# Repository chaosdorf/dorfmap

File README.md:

# dorfmap-vue

## Project setup
```
yarn install
```

### Compiles and hot-reloads for development
```
yarn run serve
```

### Compiles and minifies for production
```
yarn run build
```

### Run your tests
```
yarn run test
```

### Lints and fixes files
```
yarn run lint
```

### Customize configuration
See [Configuration Reference](https://cli.vuejs.org/config/).

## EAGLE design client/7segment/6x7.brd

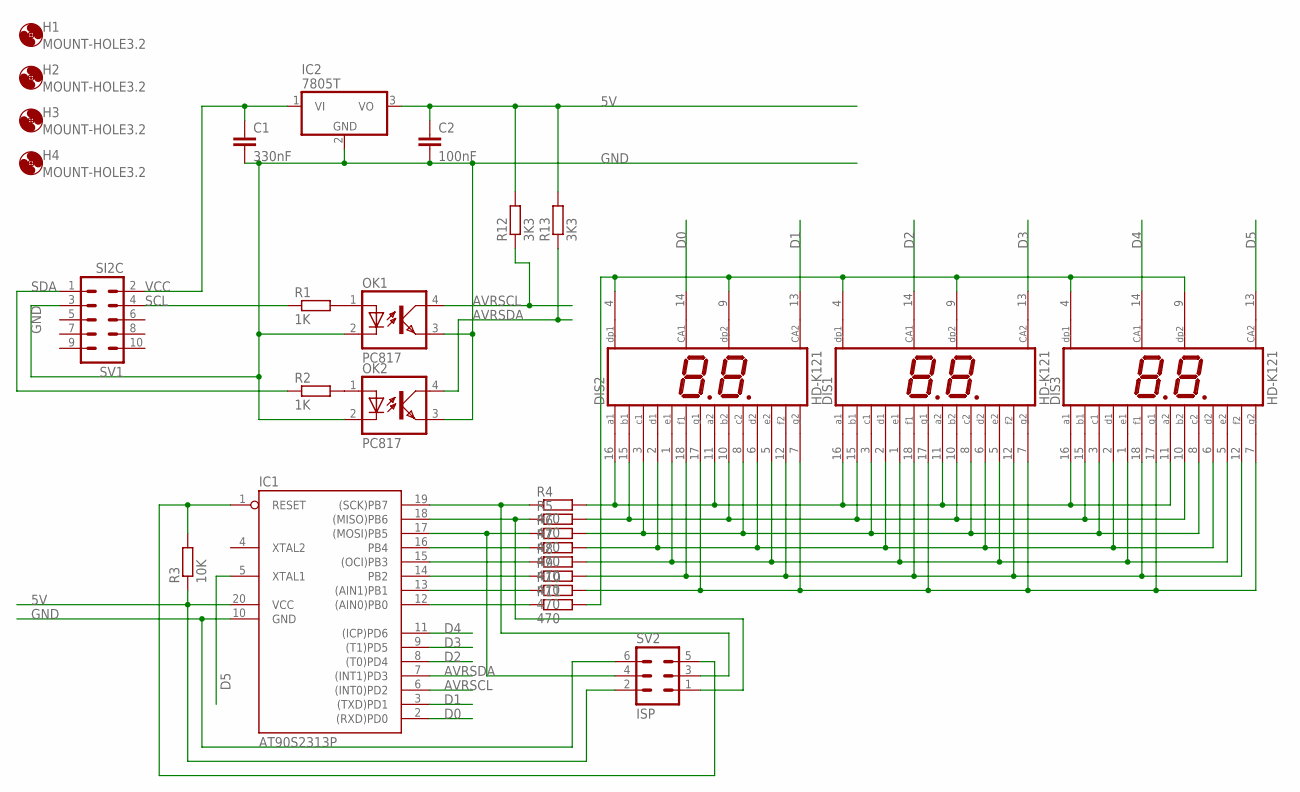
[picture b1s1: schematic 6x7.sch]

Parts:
C1: 330nF; C2.5-3
C2: 100nF; C050-024X044
DIS1, DIS2, DIS3: HD-K121; HDSP-R
H1, H2, H3, H4: MOUNT-HOLE3.2; 3,2
IC1: AT90S2313P; DIL20
IC2: 7805T; TO220H
OK1, OK2: PC817; DIL04
R1, R2: 1K; 0207/10
R3: 10K; 0207/10
R4, R5, R6, R7, R8, R9, R10, R11: 470; 0207/10
R12, R13: 3K3; 0207/10
SV1: SI2C; ML10
SV2: ISP; ML6

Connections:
5V: C2.1, IC1.20 (VCC), IC2.3 (VO), R3.1, R12.2, R13.2, SV2.2
AVRSCL: IC1.6 ((INT0)PD2), OK1.4 (COL), R12.1
AVRSDA: IC1.7 ((INT1)PD3), OK2.4 (COL), R13.1
D0: DIS2.14 (CA1), IC1.2 ((RXD)PD0)
D1: DIS2.13 (CA2), IC1.3 ((TXD)PD1)
D2: DIS1.14 (CA1), IC1.8 ((T0)PD4)
D3: DIS1.13 (CA2), IC1.9 ((T1)PD5)
D4: DIS3.14 (CA1), IC1.11 ((ICP)PD6)
D5: DIS3.13 (CA2), IC1.5 (XTAL1)
GND: C1.2, C2.2, IC1.10 (GND), IC2.2 (GND), OK1.2 (C), OK1.3 (EMIT), OK2.2 (C), OK2.3 (EMIT), SV1.3, SV2.6
unnamed: OK1.1 (A), R1.2
unnamed: IC1.19 ((SCK)PB7), R4.1, SV2.3
unnamed: IC1.1 (RESET), R3.2, SV2.5
unnamed: OK2.1 (A), R2.2
unnamed: IC1.18 ((MISO)PB6), R5.1, SV2.1
unnamed: DIS1.3 (C1), DIS1.8 (C2), DIS2.3 (C1), DIS2.8 (C2), DIS3.3 (C1), DIS3.8 (C2), R6.2
unnamed: IC1.17 ((MOSI)PB5), R6.1, SV2.4
unnamed: IC1.16 (PB4), R7.1
unnamed: IC1.15 ((OCI)PB3), R8.1
unnamed: DIS1.7 (G2), DIS1.17 (G1), DIS2.7 (G2), DIS2.17 (G1), DIS3.7 (G2), DIS3.17 (G1), R10.2
unnamed: DIS1.4 (DP1), DIS1.9 (DP2), DIS2.4 (DP1), DIS2.9 (DP2), DIS3.4 (DP1), DIS3.9 (DP2), R11.2
unnamed: IC1.14 (PB2), R9.1
unnamed: IC1.13 ((AIN1)PB1), R10.1
unnamed: IC1.12 ((AIN0)PB0), R11.1
unnamed: DIS1.11 (A2), DIS1.16 (A1), DIS2.11 (A2), DIS2.16 (A1), DIS3.11 (A2), DIS3.16 (A1), R4.2
unnamed: DIS1.10 (B2), DIS1.15 (B1), DIS2.10 (B2), DIS2.15 (B1), DIS3.10 (B2), DIS3.15 (B1), R5.2
unnamed: DIS1.2 (D1), DIS1.6 (D2), DIS2.2 (D1), DIS2.6 (D2), DIS3.2 (D1), DIS3.6 (D2), R7.2
unnamed: DIS1.1 (E1), DIS1.5 (E2), DIS2.1 (E1), DIS2.5 (E2), DIS3.1 (E1), DIS3.5 (E2), R8.2
unnamed: DIS1.12 (F2), DIS1.18 (F1), DIS2.12 (F2), DIS2.18 (F1), DIS3.12 (F2), DIS3.18 (F1), R9.2
SCL: R1.1, SV1.4
SDA: R2.1, SV1.1
VCC: C1.1, IC2.1 (VI), SV1.2

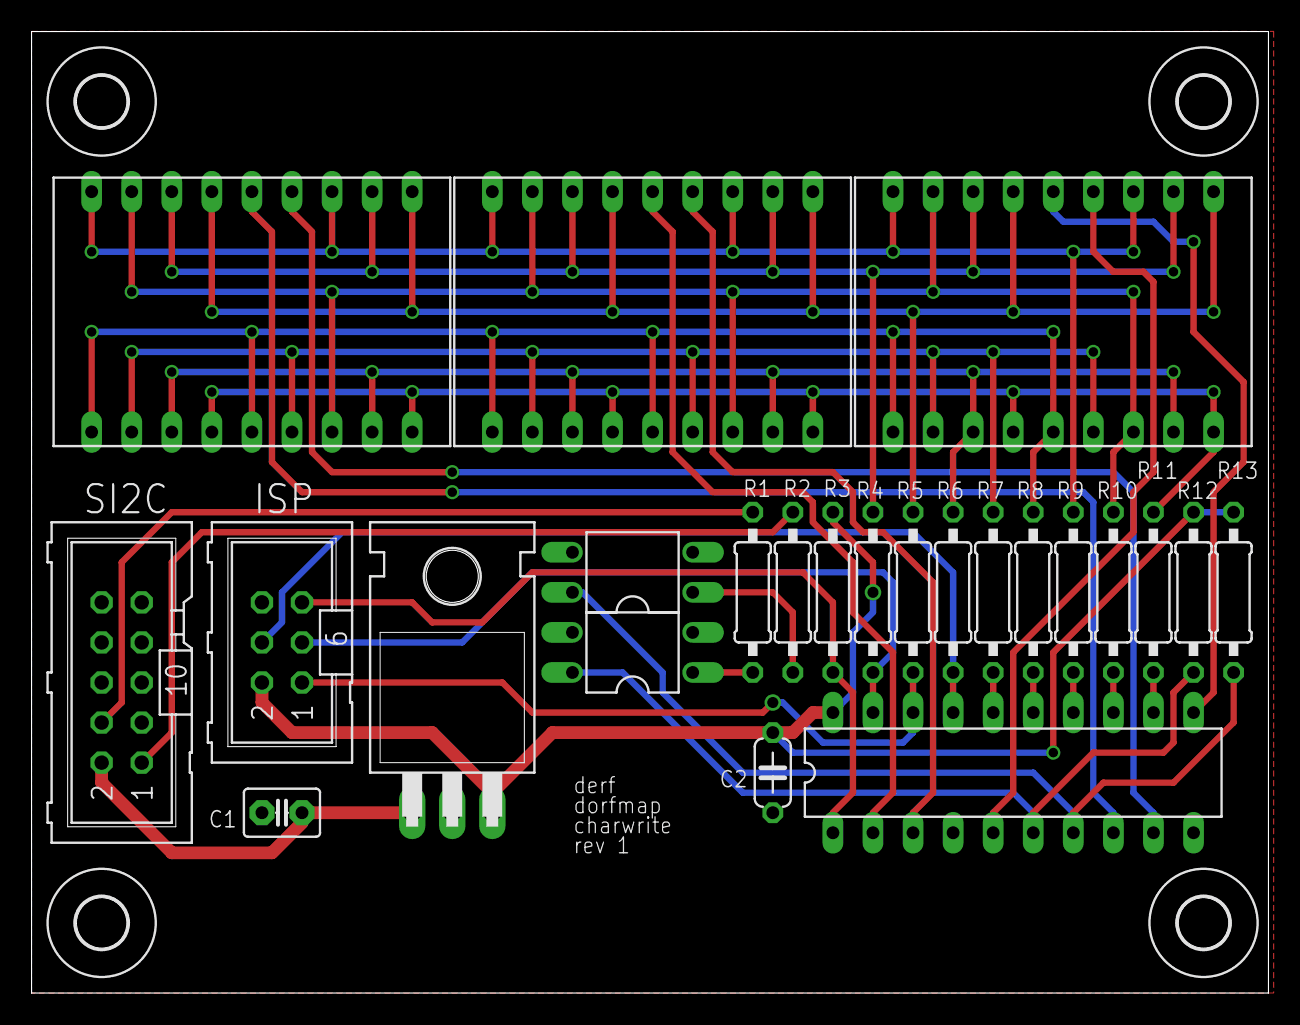
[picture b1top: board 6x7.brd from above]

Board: 2 copper layers, 78.4 x 61.0 mm, 28 parts (0 on the bottom side), 32 nets.

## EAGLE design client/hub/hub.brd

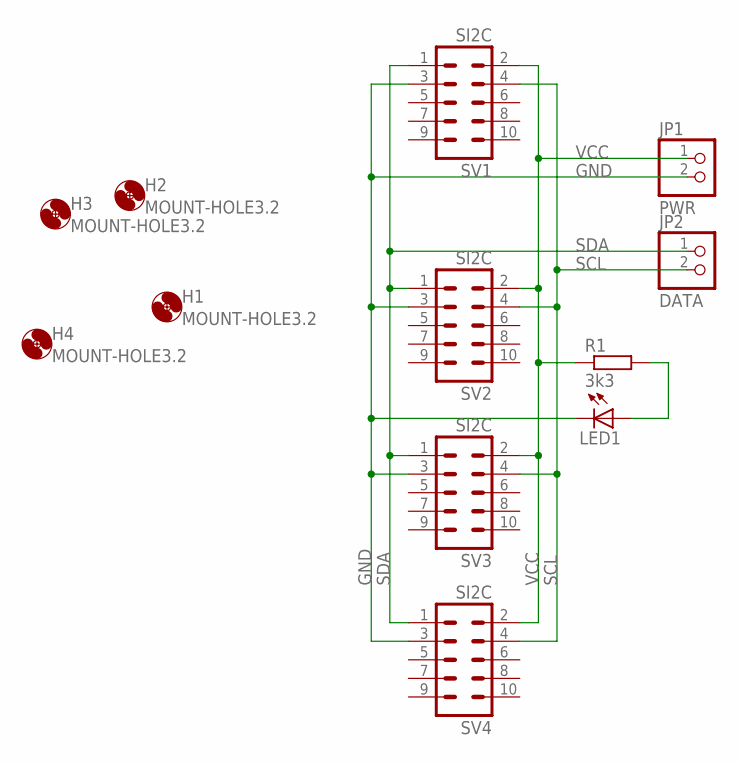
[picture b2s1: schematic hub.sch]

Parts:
H1, H2, H3, H4: MOUNT-HOLE3.2; 3,2
JP1: PWR; 1X02
JP2: DATA; 1X02
LED1: LED3MM
R1: 3k3; 0204/7
SV1, SV2, SV3, SV4: SI2C; ML10

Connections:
GND: JP1.2, LED1.K (C), SV1.3, SV2.3, SV3.3, SV4.3
unnamed: LED1.A, R1.2
SCL: JP2.2, SV1.4, SV2.4, SV3.4, SV4.4
SDA: JP2.1, SV1.1, SV2.1, SV3.1, SV4.1
VCC: JP1.1, R1.1, SV1.2, SV2.2, SV3.2, SV4.2

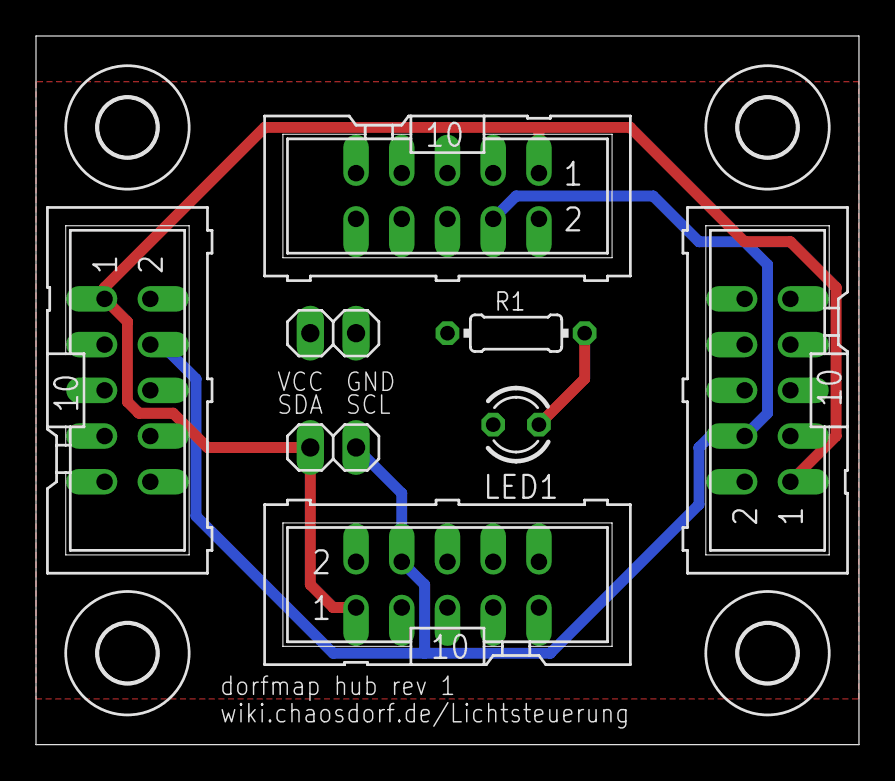
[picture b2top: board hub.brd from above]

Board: 2 copper layers, 45.7 x 39.4 mm, 12 parts (0 on the bottom side), 5 nets.

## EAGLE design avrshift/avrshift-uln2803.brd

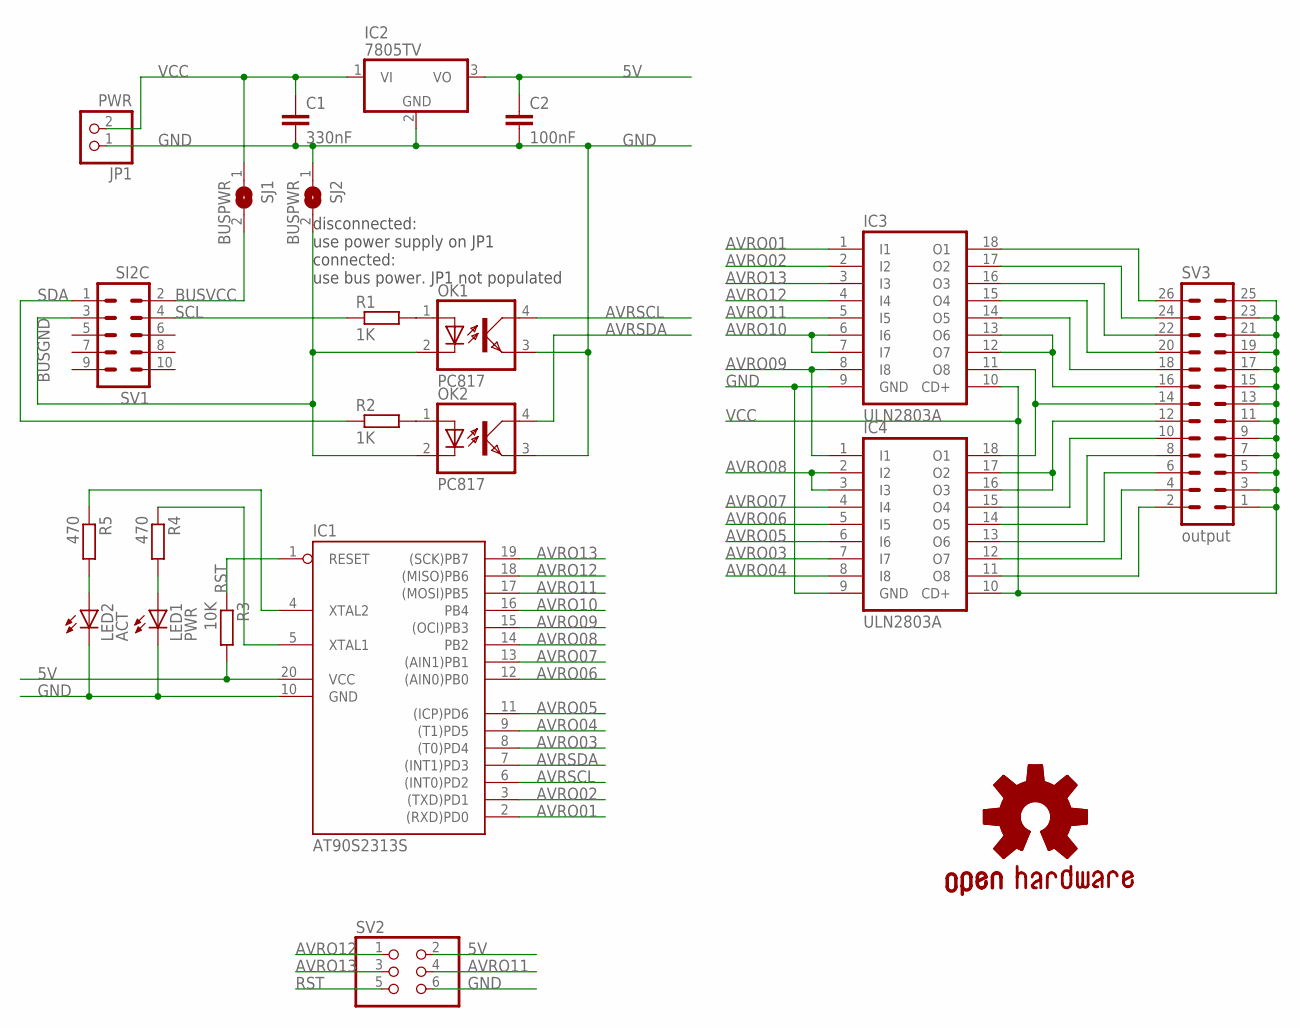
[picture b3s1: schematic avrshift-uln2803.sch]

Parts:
C1: 330nF; C2.5-3
C2: 100nF; C0805
GOLD_ORB_SM1: OSHWLOGO_GOLD_ORB_SM; OSHW2
IC1: AT90S2313S; SO20L
IC2: 7805TV; TO220V
IC3, IC4: ULN2803A; DIL18
JP1: PWR; 1X02
LED1: PWR; SML0805
LED2: ACT; SML0805
OK1, OK2: PC817; DIL04
R1, R2: 1K; R0805
R3: 10K; R0805
R4, R5: 470; R0805
SJ1, SJ2: BUSPWR; SJ
SV1: SI2C; ML10
SV2: PINHD-2X3; 2X03
SV3: output; ML26

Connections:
5V: C2.1, IC1.20 (VCC), IC2.3 (VO), R3.2, SV2.2
AVRO01: IC1.2 ((RXD)PD0), IC3.1 (I1)
AVRO02: IC1.3 ((TXD)PD1), IC3.2 (I2)
AVRO03: IC1.8 ((T0)PD4), IC4.7 (I7)
AVRO04: IC1.9 ((T1)PD5), IC4.8 (I8)
AVRO05: IC1.11 ((ICP)PD6), IC4.6 (I6)
AVRO06: IC1.12 ((AIN0)PB0), IC4.5 (I5)
AVRO07: IC1.13 ((AIN1)PB1), IC4.4 (I4)
AVRO08: IC1.14 (PB2), IC4.2 (I2), IC4.3 (I3)
AVRO09: IC1.15 ((OCI)PB3), IC3.8 (I8), IC4.1 (I1)
AVRO10: IC1.16 (PB4), IC3.6 (I6), IC3.7 (I7)
AVRO11: IC1.17 ((MOSI)PB5), IC3.5 (I5), SV2.4
AVRO12: IC1.18 ((MISO)PB6), IC3.4 (I4), SV2.1
AVRO13: IC1.19 ((SCK)PB7), IC3.3 (I3), SV2.3
AVRSCL: IC1.6 ((INT0)PD2), OK1.4 (COL)
AVRSDA: IC1.7 ((INT1)PD3), OK2.4 (COL)
BUSGND: OK1.2 (C), OK2.2 (C), SJ2.2, SV1.3
BUSVCC: SJ1.2, SV1.2
GND: C1.2, C2.2, IC1.10 (GND), IC2.2 (GND), IC3.9 (GND), IC4.9 (GND), JP1.1, LED1.C, LED2.C, OK1.3 (EMIT), OK2.3 (EMIT), SJ2.1, SV2.6
unnamed: OK1.1 (A), R1.2
unnamed: IC3.18 (O1), SV3.26
unnamed: OK2.1 (A), R2.2
unnamed: IC3.17 (O2), SV3.24
unnamed: IC3.16 (O3), SV3.22
unnamed: IC4.14 (O5), SV3.8
unnamed: LED2.A, R5.2
unnamed: IC4.13 (O6), SV3.6
unnamed: LED1.A, R4.2
unnamed: IC4.15 (O4), SV3.10
unnamed: IC4.16 (O3), IC4.17 (O2), SV3.12
unnamed: IC3.11 (O8), IC4.18 (O1), SV3.14
unnamed: IC3.12 (O7), IC3.13 (O6), SV3.16
unnamed: IC3.14 (O5), SV3.18
unnamed: IC4.12 (O7), SV3.4
unnamed: IC4.11 (O8), SV3.2
unnamed: IC1.4 (XTAL2), R5.1
unnamed: IC3.15 (O4), SV3.20
unnamed: IC1.5 (XTAL1), R4.1
RST: IC1.1 (RESET), R3.1, SV2.5
SCL: R1.1, SV1.4
SDA: R2.1, SV1.1
VCC: C1.1, IC2.1 (VI), IC3.10 (CD+), IC4.10 (CD+), JP1.2, SJ1.1, SV3.1, SV3.3, SV3.5, SV3.7, SV3.9, SV3.11, SV3.13, SV3.15, SV3.17, SV3.19, SV3.21, SV3.23, SV3.25

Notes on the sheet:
disconnected: use power supply on JP1 connected: use bus power. JP1 not populated

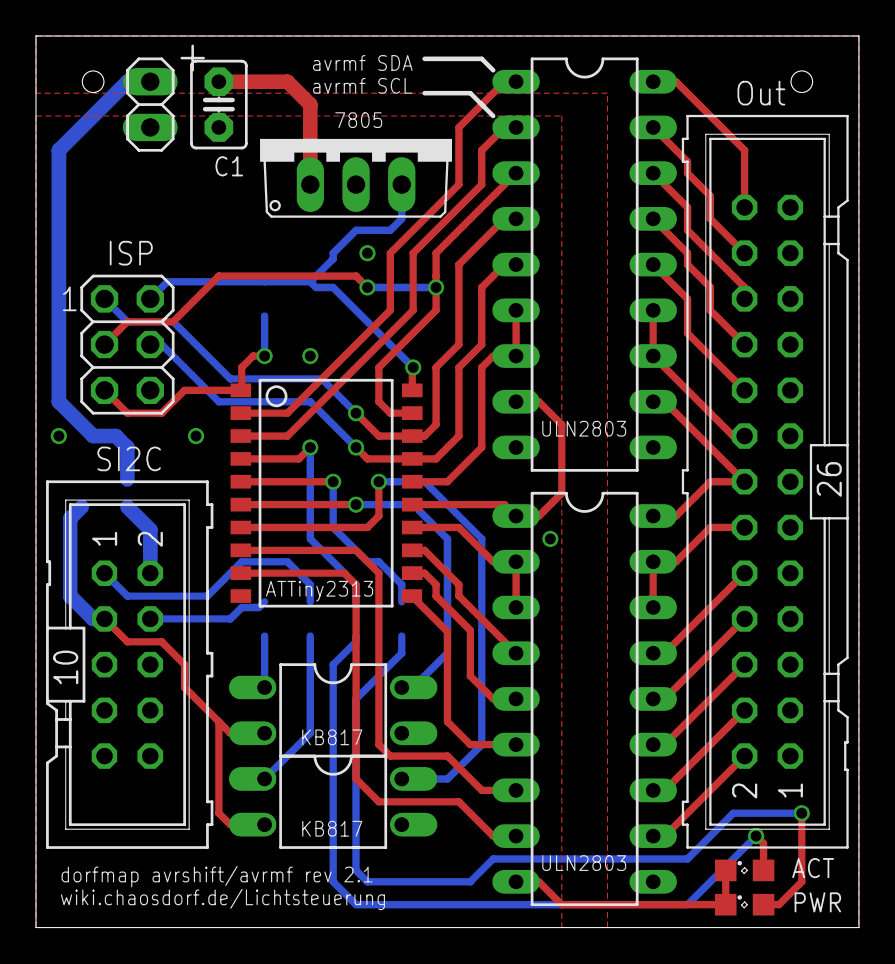
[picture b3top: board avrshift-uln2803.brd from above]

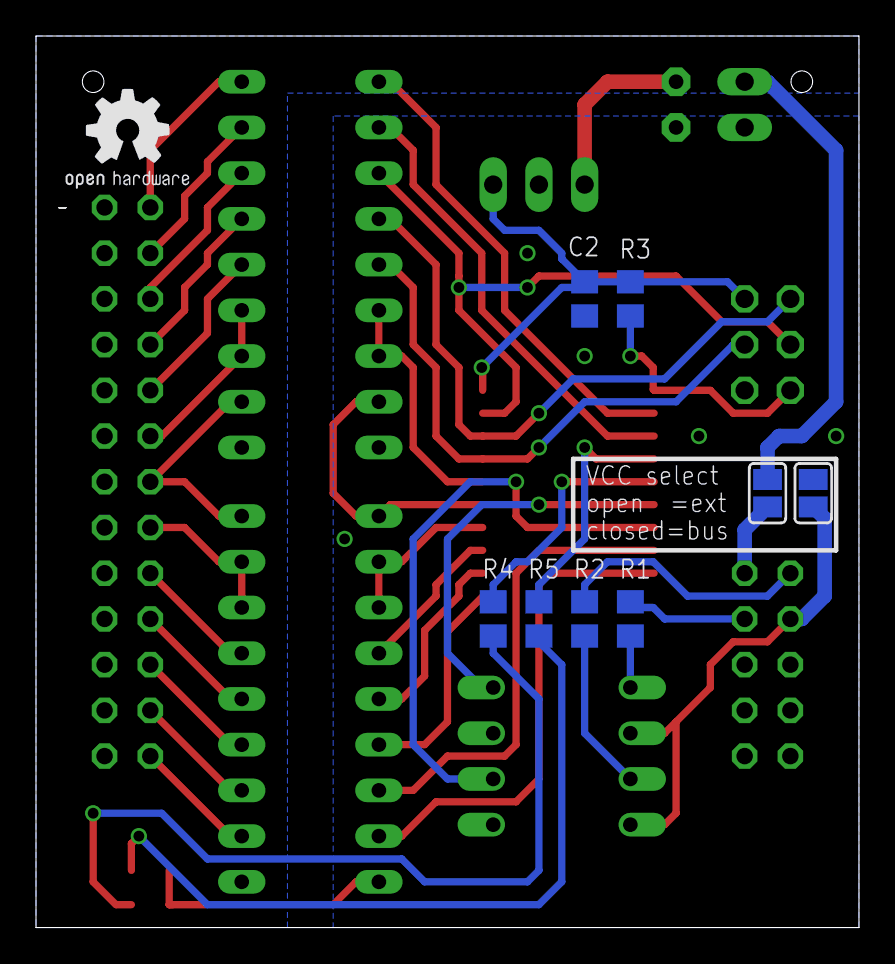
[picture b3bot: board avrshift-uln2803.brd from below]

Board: 2 copper layers, 45.7 x 49.5 mm, 22 parts (9 on the bottom side), 42 nets.

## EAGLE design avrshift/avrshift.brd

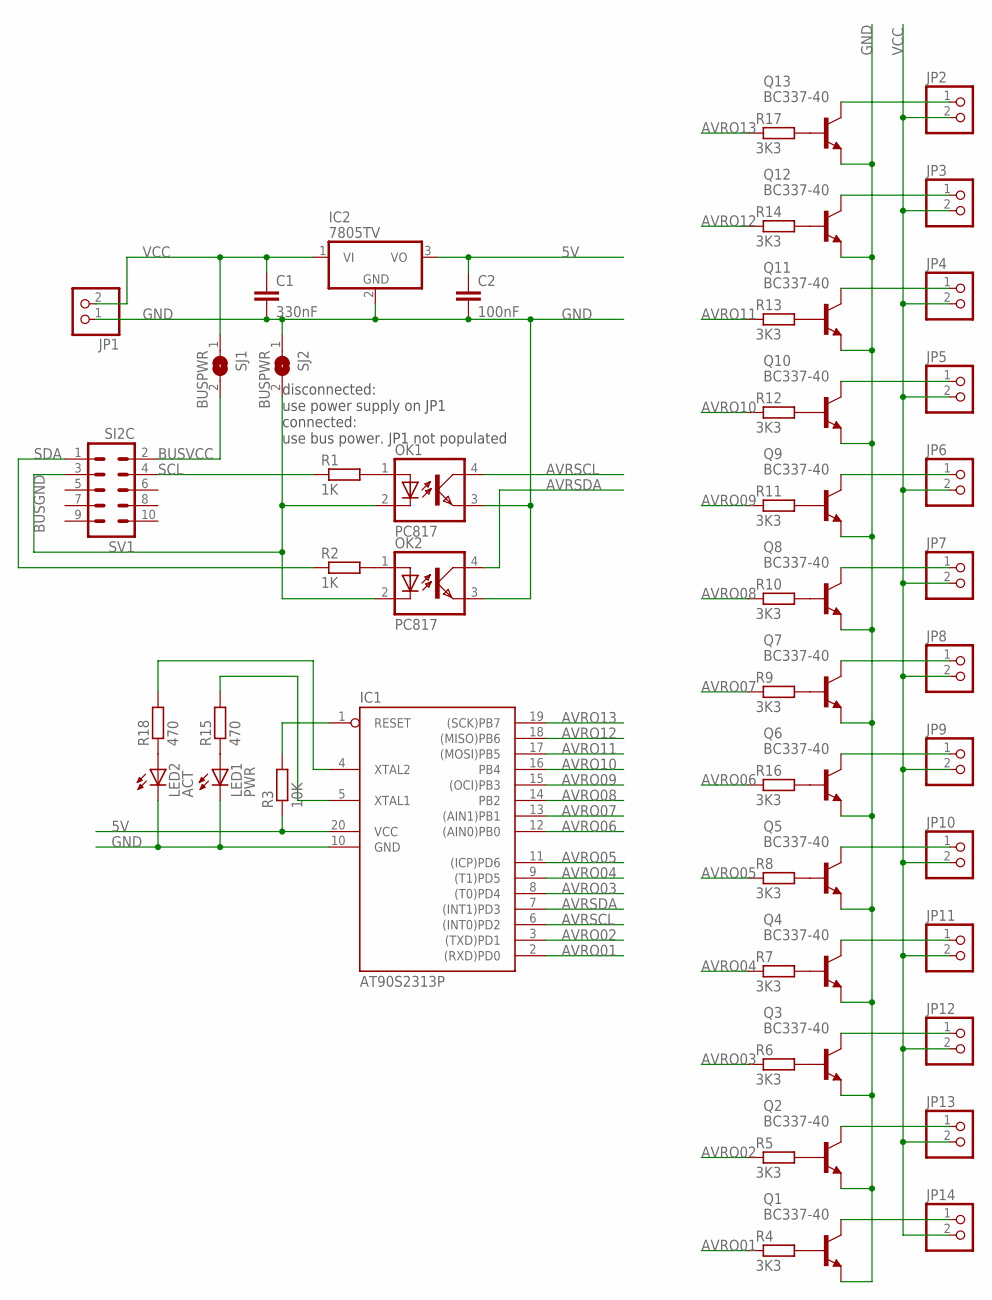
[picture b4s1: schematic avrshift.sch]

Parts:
C1: 330nF; C2.5-3
C2: 100nF; C2.5-3
IC1: AT90S2313P; DIL20
IC2: 7805TV; TO220V
JP1, JP2, JP3, JP4, JP5, JP6, JP7, JP8, JP9, JP10, JP11, JP12, JP13, JP14: PINHD-1X2; 1X02
LED1: PWR; LED3MM
LED2: ACT; LED3MM
OK1, OK2: PC817; DIL04
Q1, Q2, Q3, Q4, Q5, Q6, Q7, Q8, Q9, Q10, Q11, Q12, Q13: BC337-40; TO92
R1, R2: 1K; 0207/10
R3: 10K; 0207/10
R4, R5, R6, R7, R8, R9, R10, R11, R12, R13, R14, R16, R17: 3K3; 0207/10
R15, R18: 470; 0207/10
SJ1, SJ2: BUSPWR; SJ
SV1: SI2C; ML10

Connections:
5V: C2.1, IC1.20 (VCC), IC2.3 (VO), R3.1
AVRO01: IC1.2 ((RXD)PD0), R4.1
AVRO02: IC1.3 ((TXD)PD1), R5.1
AVRO03: IC1.8 ((T0)PD4), R6.1
AVRO04: IC1.9 ((T1)PD5), R7.1
AVRO05: IC1.11 ((ICP)PD6), R8.1
AVRO06: IC1.12 ((AIN0)PB0), R16.1
AVRO07: IC1.13 ((AIN1)PB1), R9.1
AVRO08: IC1.14 (PB2), R10.1
AVRO09: IC1.15 ((OCI)PB3), R11.1
AVRO10: IC1.16 (PB4), R12.1
AVRO11: IC1.17 ((MOSI)PB5), R13.1
AVRO12: IC1.18 ((MISO)PB6), R14.1
AVRO13: IC1.19 ((SCK)PB7), R17.1
AVRSCL: IC1.6 ((INT0)PD2), OK1.4 (COL)
AVRSDA: IC1.7 ((INT1)PD3), OK2.4 (COL)
BUSGND: OK1.2 (C), OK2.2 (C), SJ2.2, SV1.3
BUSVCC: SJ1.2, SV1.2
GND: C1.2, C2.2, IC1.10 (GND), IC2.2 (GND), JP1.1, LED1.K (C), LED2.K (C), OK1.3 (EMIT), OK2.3 (EMIT), Q1.1 (E), Q2.1 (E), Q3.1 (E), Q4.1 (E), Q5.1 (E), Q6.1 (E), Q7.1 (E), Q8.1 (E), Q9.1 (E), Q10.1 (E), Q11.1 (E), Q12.1 (E), Q13.1 (E), SJ2.1
unnamed: OK1.1 (A), R1.2
unnamed: IC1.1 (RESET), R3.2
unnamed: OK2.1 (A), R2.2
unnamed: Q13.2 (B), R17.2
unnamed: JP13.1, Q2.3 (C)
unnamed: JP2.1, Q13.3 (C)
unnamed: LED2.A, R18.1
unnamed: Q1.2 (B), R4.2
unnamed: LED1.A, R15.1
unnamed: Q2.2 (B), R5.2
unnamed: Q3.2 (B), R6.2
unnamed: Q4.2 (B), R7.2
unnamed: Q5.2 (B), R8.2
unnamed: Q7.2 (B), R9.2
unnamed: Q8.2 (B), R10.2
unnamed: Q9.2 (B), R11.2
unnamed: Q10.2 (B), R12.2
unnamed: Q11.2 (B), R13.2
unnamed: Q12.2 (B), R14.2
unnamed: IC1.4 (XTAL2), R18.2
unnamed: Q6.2 (B), R16.2
unnamed: JP3.1, Q12.3 (C)
unnamed: IC1.5 (XTAL1), R15.2
unnamed: JP14.1, Q1.3 (C)
unnamed: JP12.1, Q3.3 (C)
unnamed: JP11.1, Q4.3 (C)
unnamed: JP10.1, Q5.3 (C)
unnamed: JP9.1, Q6.3 (C)
unnamed: JP8.1, Q7.3 (C)
unnamed: JP7.1, Q8.3 (C)
unnamed: JP6.1, Q9.3 (C)
unnamed: JP5.1, Q10.3 (C)
unnamed: JP4.1, Q11.3 (C)
SCL: R1.1, SV1.4
SDA: R2.1, SV1.1
VCC: C1.1, IC2.1 (VI), JP1.2, JP2.2, JP3.2, JP4.2, JP5.2, JP6.2, JP7.2, JP8.2, JP9.2, JP10.2, JP11.2, JP12.2, JP13.2, JP14.2, SJ1.1

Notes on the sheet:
disconnected: use power supply on JP1 connected: use bus power. JP1 not populated

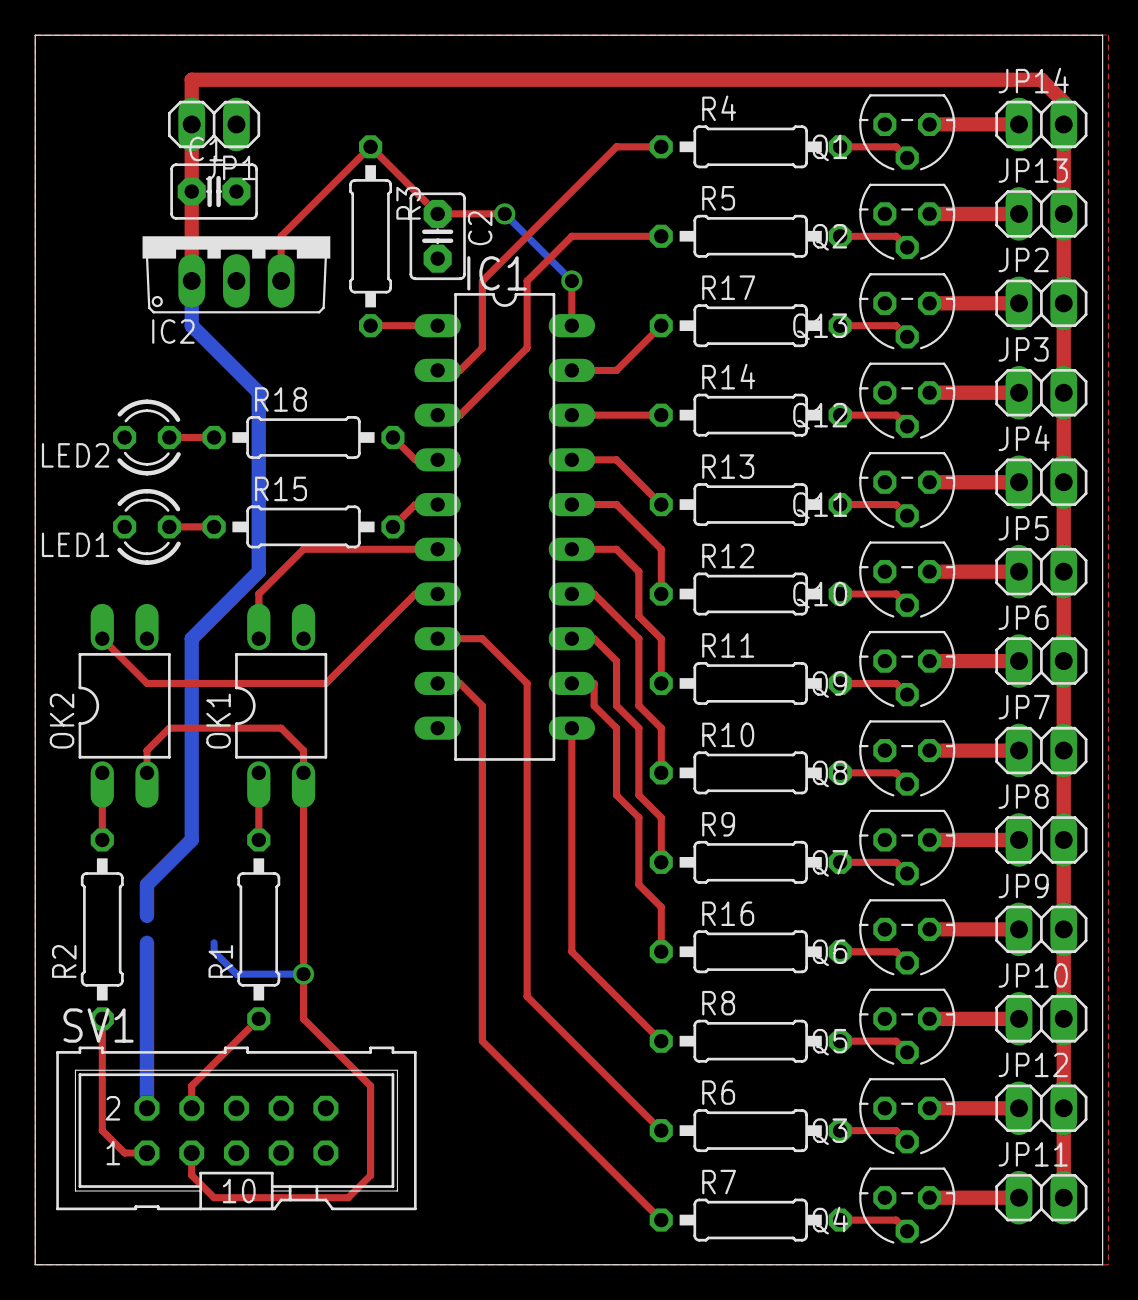
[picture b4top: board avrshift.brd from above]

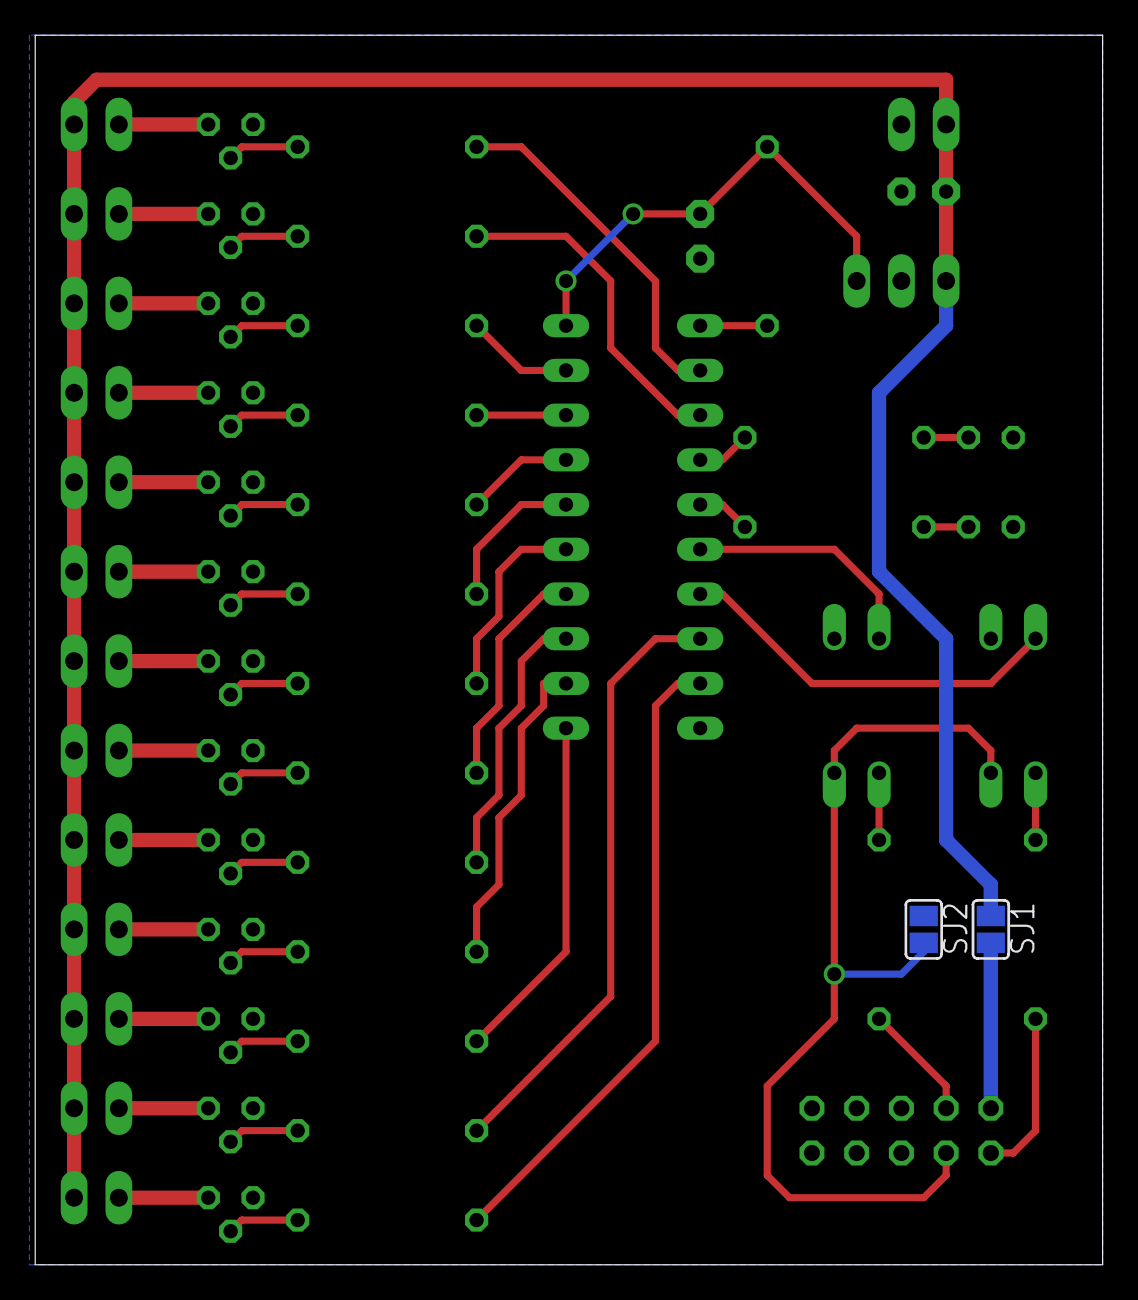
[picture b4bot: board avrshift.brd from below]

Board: 2 copper layers, 60.6 x 69.8 mm, 56 parts (2 on the bottom side), 55 nets.

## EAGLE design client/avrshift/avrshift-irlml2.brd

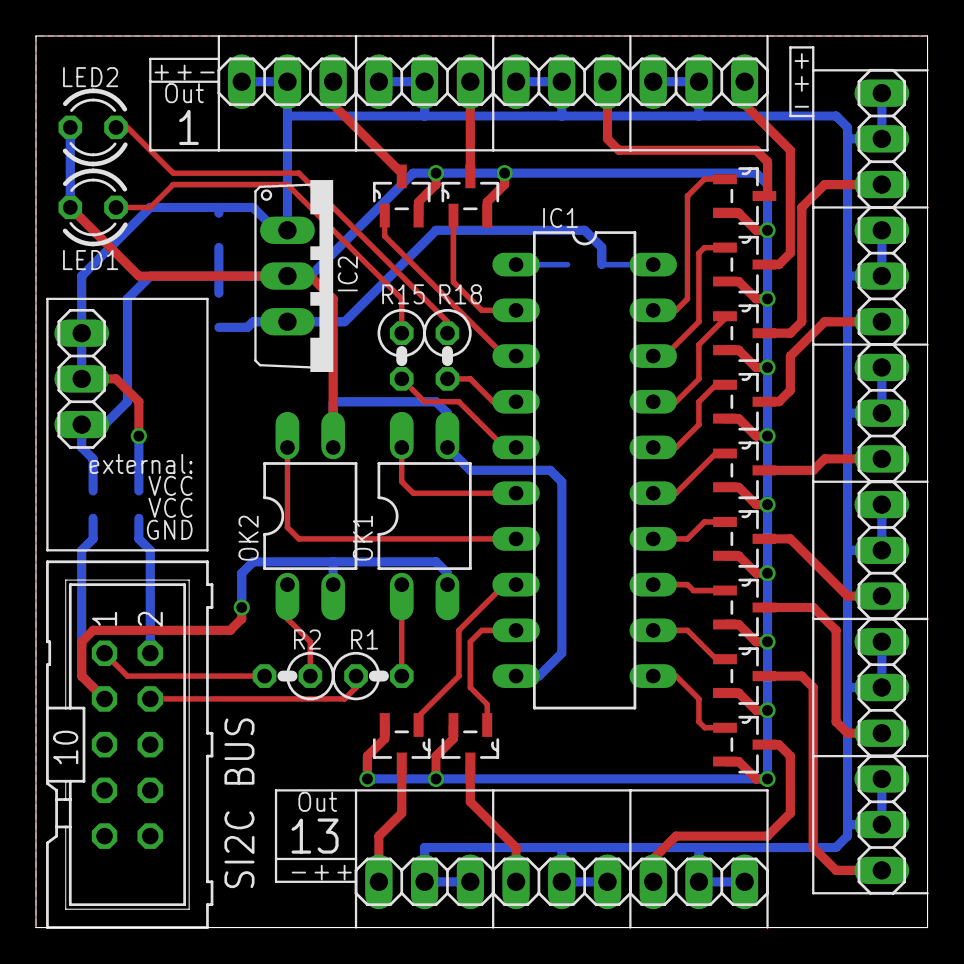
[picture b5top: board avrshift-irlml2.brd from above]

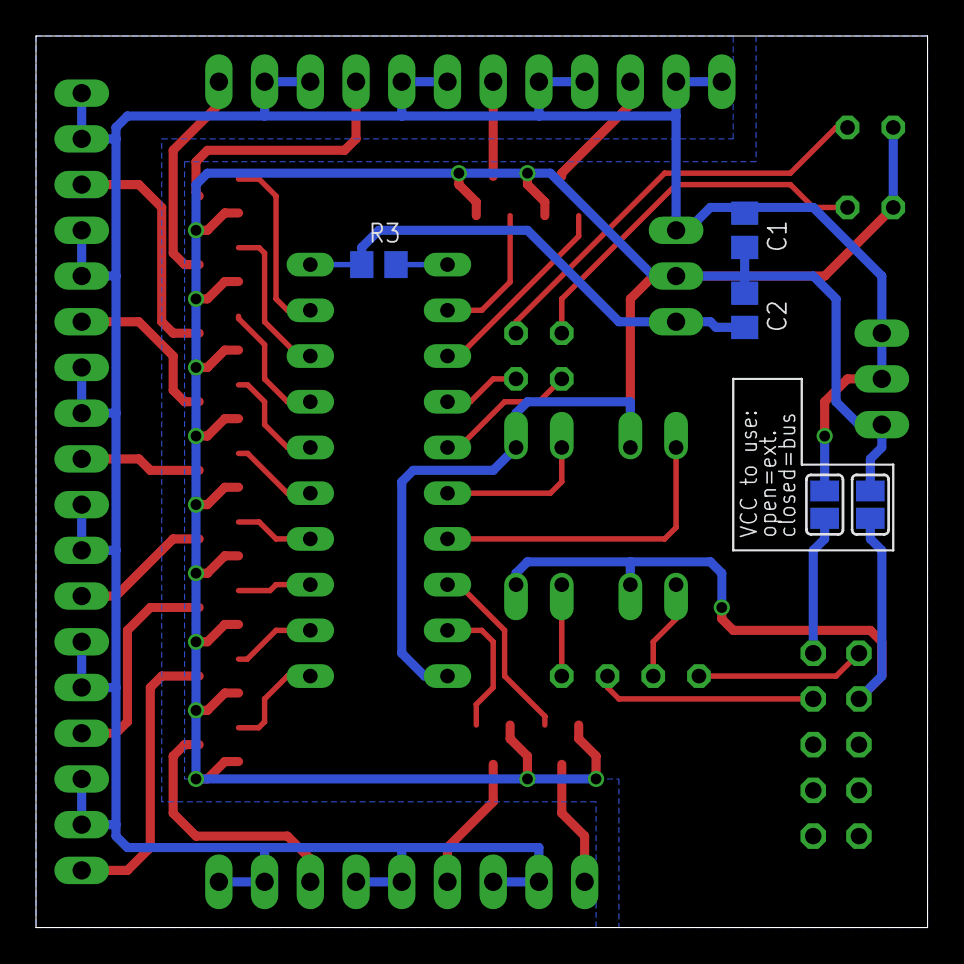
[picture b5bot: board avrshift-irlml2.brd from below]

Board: 2 copper layers, 49.5 x 49.5 mm, 43 parts (5 on the bottom side), 42 nets.

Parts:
C1: 330nF; C0805
C2: 100nF; C0805
IC1: AT90S2313P; DIL20
IC2: 7805TV; TO220V
JP1: PWR; 1X03
JP2, JP3, JP4, JP5, JP6, JP7, JP8, JP9, JP10, JP11, JP12, JP13, JP14: 1X03
LED1: PWR; LED3MM
LED2: ACT; LED3MM
OK1, OK2: PC817; DIL04
R1, R2: 1K; 0207/2V
R3: 10K; R0805
R15, R18: 470; 0207/2V
SJ1, SJ2: BUSPWR; SJ
SV1: SI2C; ML10
U1, U2, U3, U4, U5, U6, U7, U8, U9, U10, U11, U12, U13: IRFML8244TRPBF; SOT95P240X112-3N

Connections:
5V: C2.1, IC1.20, IC2.3, R3.1
AVRSCL: IC1.6, OK1.4
AVRSDA: IC1.7, OK2.4
BUSGND: OK1.2, OK2.2, SJ2.2, SV1.3
BUSVCC: SJ1.2, SV1.2
GND: C1.2, C2.2, IC1.10, IC2.2, JP1.1, LED1.K, LED2.K, OK1.3, OK2.3, SJ2.1, U1.2, U2.2, U3.2, U4.2, U5.2, U6.2, U7.2, U8.2, U9.2, U10.2, U11.2, U12.2, U13.2
unnamed: OK1.1, R1.2
unnamed: JP2.1, U1.3
unnamed: OK2.1, R2.1
unnamed: JP3.1, U2.3
unnamed: JP4.1, U3.3
unnamed: JP11.1, U10.3
unnamed: LED2.A, R18.1
unnamed: JP12.1, U11.3
unnamed: LED1.A, R15.1
unnamed: JP10.1, U9.3
unnamed: JP9.1, U8.3
unnamed: JP8.1, U7.3
unnamed: JP7.1, U6.3
unnamed: JP6.1, U5.3
unnamed: JP13.1, U12.3
unnamed: JP14.1, U13.3
unnamed: IC1.4, R18.2
unnamed: JP5.1, U4.3
unnamed: IC1.5, R15.2
OUT1: IC1.3, U1.1
OUT2: IC1.2, U2.1
OUT3: IC1.19, U3.1
OUT4: IC1.18, U4.1
OUT5: IC1.17, U5.1
OUT6: IC1.16, U6.1
OUT7: IC1.15, U7.1
OUT8: IC1.14, U8.1
OUT9: IC1.13, U9.1
OUT10: IC1.12, U10.1
OUT11: IC1.11, U11.1
OUT12: IC1.9, U12.1
OUT13: IC1.8, U13.1
RESET: IC1.1, R3.2
SCL: R1.1, SV1.4
SDA: R2.2, SV1.1
VCC: C1.1, IC2.1, JP1.2, JP1.3, JP2.2, JP2.3, JP3.2, JP3.3, JP4.2, JP4.3, JP5.2, JP5.3, JP6.2, JP6.3, JP7.2, JP7.3, JP8.2, JP8.3, JP9.2, JP9.3, JP10.2, JP10.3, JP11.2, JP11.3, JP12.2, JP12.3, JP13.2, JP13.3, JP14.2, JP14.3, SJ1.1

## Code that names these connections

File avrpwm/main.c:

#include <avr/interrupt.h>
#include <avr/io.h>
#include <math.h>
#include <stdlib.h>

/*
 * PA0, PA1: status LED
 * PD0, PD1, PD4, PD6: binary out
 * PB0, PB1, PB5, PB6, PB7: binary out
 * PB2, PB3, PB4, PD5: analog out (pwm)
 */

/*
 * PD2 and PD3 are inverted (optokoppler to gnd and internal pull-ups)
 */
#define CLOCK_LO ( ( PIND & _BV(PD2) ) != 0 )
#define CLOCK_HI ( ( PIND & _BV(PD2) ) == 0 )
#define DATA_LO ( ( PIND & _BV(PD3) ) != 0 )
#define DATA_HI ( ( PIND & _BV(PD3) ) == 0 )
#define DATA_BIT ( ( ~PIND & _BV(PD3) ) >> PD3 )

#define MYADDRESS (0x000d)

volatile uint8_t binary_1 = 0;
volatile uint8_t binary_2 = 0;
volatile uint8_t pwm[4];
volatile uint16_t address;

int main (void)
{
	uint16_t start_delay;

	/* watchdog reset after ~4 seconds */
	MCUSR &= ~_BV(WDRF);
	WDTCSR = _BV(WDCE) | _BV(WDE);
	WDTCSR = _BV(WDE) | _BV(WDP3);

	ACSR |= _BV(ACD);

	DDRA = _BV(0);
	DDRB = 0xff;
	DDRD = _BV(DDD0) | _BV(DDD1) | _BV(DDD4) | _BV(DDD5) | _BV(DDD6);

	PORTB = 0;
	PORTD = _BV(PD2) | _BV(PD3);

	MCUCR |= _BV(ISC00);
	GIMSK |= _BV(INT0);

	/* disabled fast PWM on OC0A and OC0B, interrupt on overflow*/
	TCCR0A = _BV(WGM01) | _BV(WGM00);
	TCCR0B = _BV(CS00);
	TIMSK = _BV(TOIE0);

	/* disabled 8-bit fast PWM on OC1A and OC1B */
	TCCR1A = _BV(WGM10);
	TCCR1B = _BV(WGM12) | _BV(CS00);

	for (start_delay = 0; start_delay < 0xff; start_delay++)
		asm("nop");

	sei();

	while (1) {
		MCUCR |= _BV(SE);
		asm("sleep");
	}

	return 0;
}

static void apply_pwm(void)
{
	if (OCR0A)
		TCCR0A |= _BV(COM0A1);
	else
		TCCR0A &= ~_BV(COM0A1);

	if (OCR0B)
		TCCR0A |= _BV(COM0B1);
	else
		TCCR0A &= ~_BV(COM0B1);

	if (OCR1A)
		TCCR1A |= _BV(COM1A1);
	else
		TCCR1A &= ~_BV(COM1A1);

	if (OCR1B)
		TCCR1A |= _BV(COM1B1);
	else
		TCCR1A &= ~_BV(COM1B1);
}

ISR(INT0_vect)
{
	if (CLOCK_HI) {
		// rising clock: read data
		binary_1 = (binary_1 << 1) | (binary_2 >> 7);
		binary_2 = (binary_2 << 1) | (pwm[3] >> 7);
		pwm[3] = (pwm[3] << 1) | (pwm[2] >> 7);
		pwm[2] = (pwm[2] << 1) | (pwm[1] >> 7);
		pwm[1] = (pwm[1] << 1) | (pwm[0] >> 7);
		pwm[0] = (pwm[0] << 1) | (address >> 15);
		address = (address << 1) | DATA_BIT;

		if (DATA_BIT != 0)
			PORTA |= _BV(PA0);
		else
			PORTA &= ~_BV(PA0);
	}
	else {
		if (DATA_HI && (address == MYADDRESS)) {
			// falling clock, data is high: end of transmission

			PORTB = binary_1
				& ( _BV(0) | _BV(1) | _BV(5) | _BV(6) | _BV(7) );

			PORTD = _BV(PD2) | _BV(PD3) | (binary_2
				& ( _BV(0) | _BV(1) | _BV(4) | _BV(6) ));


			OCR0A = pwm[0];
			OCR0B = pwm[1];
			OCR1A = pwm[2];
			OCR1B = pwm[3];
			apply_pwm();
		}
	}
}

ISR(TIMER0_OVF_vect)
{
	asm("wdr");
}
